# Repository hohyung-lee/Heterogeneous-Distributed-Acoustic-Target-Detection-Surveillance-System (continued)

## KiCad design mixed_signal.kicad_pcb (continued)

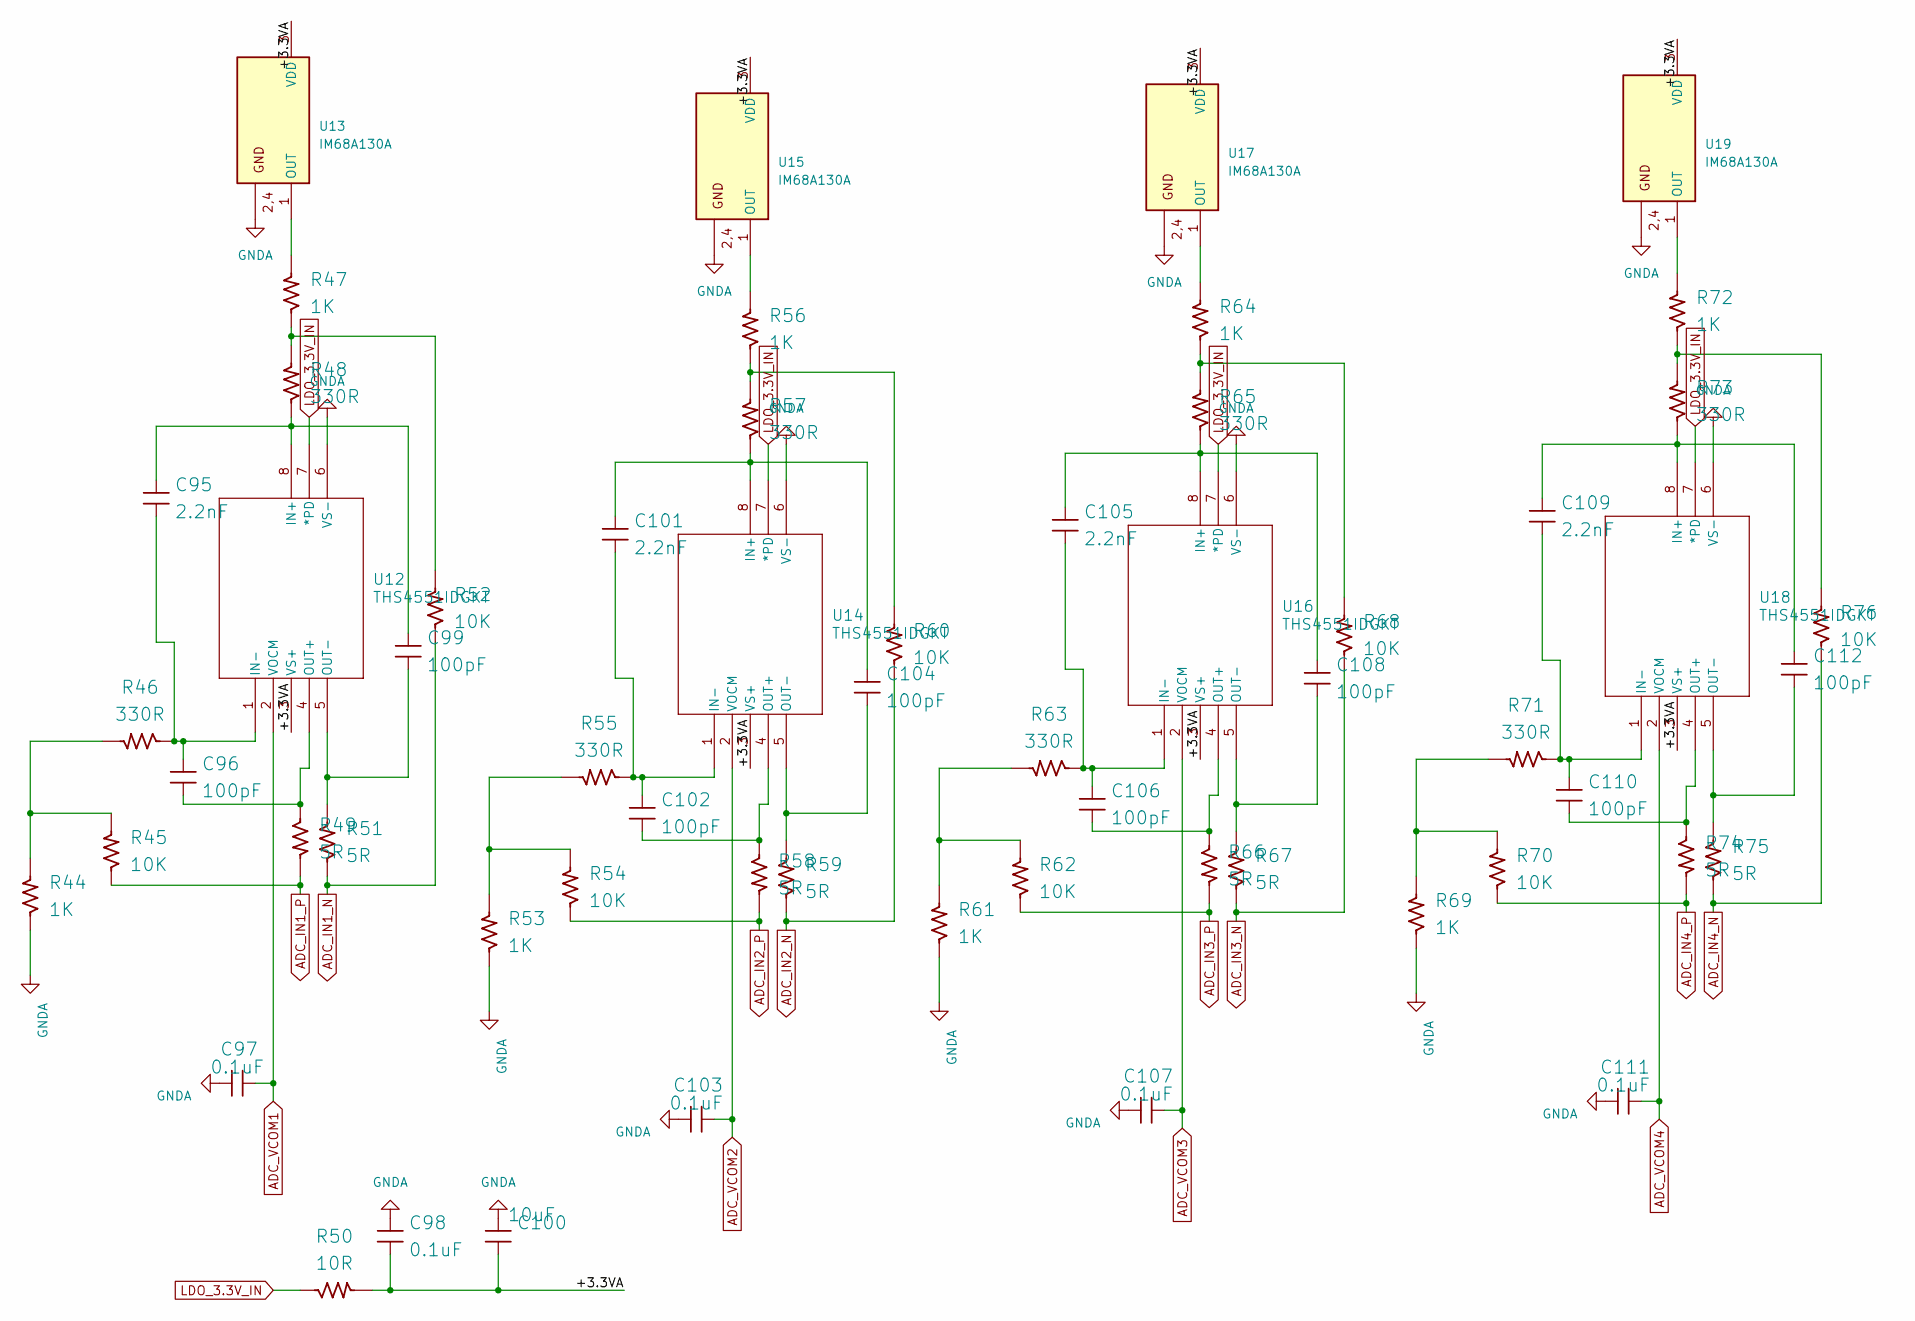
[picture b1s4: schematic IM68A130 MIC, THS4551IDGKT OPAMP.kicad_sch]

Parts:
C95, C101, C105, C109: 2.2nF; CAP_0805; Manufacturer Part Number C0805C222K5GEC7800
C96, C99, C102, C104, C106, C108, C110, C112: 100pF; CAP_0805; Manufacturer Part Number CC0805JRNPO9BN101
C97, C98, C103, C107, C111: 0.1uF; CAP_0805; Manufacturer Part Number 08055C104JAT4A
C100: 10uF; CAP_1206; Manufacturer Part Number CL31B106KBHNNNE
R44, R47, R53, R56, R61, R64, R69, R72: 1K; RES_0805; Manufacturer Part Number WR08X1001FTL
R45, R52, R54, R60, R62, R68, R70, R76: 10K; RES_0805; Manufacturer Part Number WR08X1002FTL
R46, R48, R55, R57, R63, R65, R71, R73: 330R; RES_0805; Manufacturer Part Number WR08X3300FTL
R49, R51, R58, R59, R66, R67, R74, R75: 5R; RES_0805; Manufacturer Part Number L-0805M5R00FGTS
R50: 10R; RES_0805; Manufacturer Part Number WR08X10R0FTL
U12, U14, U16, U18: THS4551IDGKT; DGK_S-PDSO-G8_TEX
U13, U15, U17, U19: IM68A130A; PAP0064G-IPC_A

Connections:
/IM68A130 MIC, THS4551IDGKT OPAMP/+3.3VA: C98.1, C100.1, R50.2, U12.3 (VS+), U13.3 (VDD), U14.3 (VS+), U15.3 (VDD), U16.3 (VS+), U17.3 (VDD), U18.3 (VS+), U19.3 (VDD)
ADC_IN1_N: R51.1, R52.1; also elsewhere on the board
ADC_IN1_P: R45.1, R49.2; also elsewhere on the board
ADC_IN2_N: R59.1, R60.1; also elsewhere on the board
ADC_IN2_P: R54.1, R58.2; also elsewhere on the board
ADC_IN3_N: R67.1, R68.1; also elsewhere on the board
ADC_IN3_P: R62.1, R66.2; also elsewhere on the board
ADC_IN4_N: R75.1, R76.1; also elsewhere on the board
ADC_IN4_P: R70.1, R74.2; also elsewhere on the board
ADC_VCOM1: C97.2, C103.2, C107.2, C111.2, U12.2 (VOCM), U14.2 (VOCM), U16.2 (VOCM), U18.2 (VOCM); also elsewhere on the board
GNDA: C97.1, C98.2, C100.2, C103.1, C107.1, C111.1, R44.1, R53.1, R61.1, R69.1, U12.6 (VS-), U13.2 (GND), U13.4 (GND), U14.6 (VS-), U15.2 (GND), U15.4 (GND), U16.6 (VS-), U17.2 (GND), U17.4 (GND), U18.6 (VS-), U19.2 (GND), U19.4 (GND); also elsewhere on the board
LDO_3.3V_IN: R50.1, U12.7 (*PD), U14.7 (*PD), U16.7 (*PD), U18.7 (*PD); also elsewhere on the board
unnamed: R44.2, R45.2, R46.2
unnamed: R47.1, R48.2, R52.2
unnamed: R53.2, R54.2, R55.2
unnamed: R56.1, R57.2, R60.2
unnamed: R61.2, R62.2, R63.2
unnamed: R64.1, R65.2, R68.2
unnamed: R69.2, R70.2, R71.2
unnamed: R72.1, R73.2, R76.2
unnamed: C95.2, C99.2, R48.1, U12.8 (IN+)
unnamed: C95.1, C96.2, R46.1, U12.1 (IN-)
unnamed: C96.1, R49.1, U12.4 (OUT+)
unnamed: C99.1, R51.2, U12.5 (OUT-)
unnamed: R47.2, U13.1 (OUT)
unnamed: C101.2, C104.2, R57.1, U14.8 (IN+)
unnamed: C101.1, C102.2, R55.1, U14.1 (IN-)
unnamed: C102.1, R58.1, U14.4 (OUT+)
unnamed: C104.1, R59.2, U14.5 (OUT-)
unnamed: R56.2, U15.1 (OUT)
unnamed: C105.2, C108.2, R65.1, U16.8 (IN+)
unnamed: C105.1, C106.2, R63.1, U16.1 (IN-)
unnamed: C106.1, R66.1, U16.4 (OUT+)
unnamed: C108.1, R67.2, U16.5 (OUT-)
unnamed: R64.2, U17.1 (OUT)
unnamed: C109.2, C112.2, R73.1, U18.8 (IN+)
unnamed: C109.1, C110.2, R71.1, U18.1 (IN-)
unnamed: C110.1, R74.1, U18.4 (OUT+)
unnamed: C112.1, R75.2, U18.5 (OUT-)
unnamed: R72.2, U19.1 (OUT)

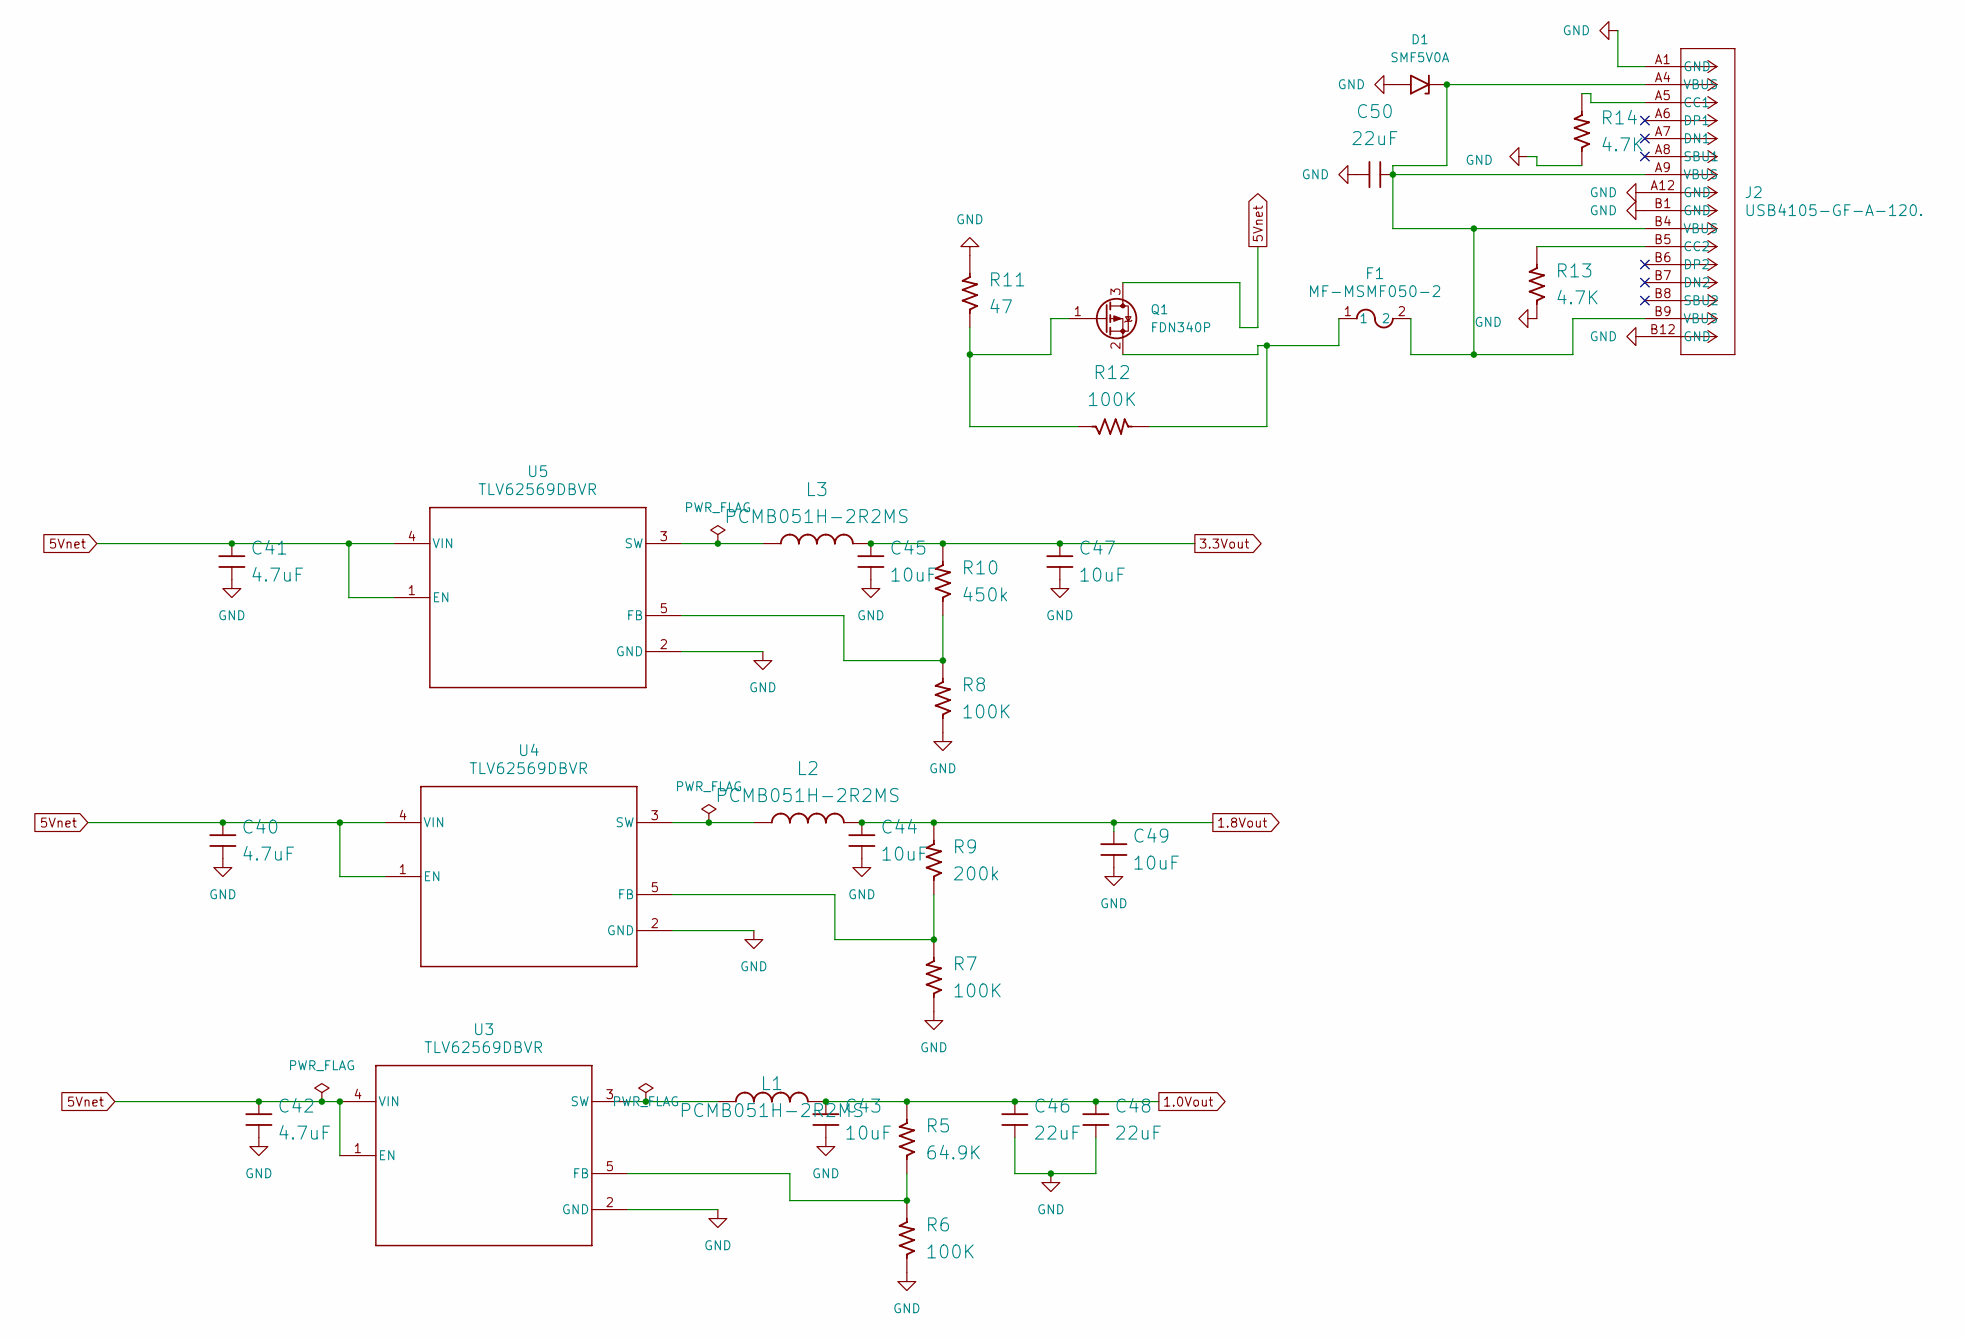
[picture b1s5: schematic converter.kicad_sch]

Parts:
C40, C41, C42: 4.7uF; CAP_0805; Manufacturer Part Number GRM21BR61H475KE51L
C43, C44, C45, C47, C49: 10uF; CAP_1206; Manufacturer Part Number CL31B106KBHNNNE
C46, C48, C50: 22uF; CAP_0805; Manufacturer Part Number GRM21BR61E226ME44L
D1: SMF5V0A; D_SMF
F1: MF-MSMF050-2; FUSE_F050-2
J2: USB4105-GF-A-120.; CONN_USB4105-xx-A-xxx_GCT
L1, L2, L3: PCMB051H-2R2MS; IND_259_338_140X70_SMD; Manufacturer Part Number PCMB051H-2R2MS
Q1: FDN340P; SOT-23
R5: 64.9K; RES_0805; Manufacturer Part Number RC0805FR-0764K9L
R6, R7, R8, R12: 100K; RES_0805; Manufacturer Part Number WR08X1003FTL
R9: 200k; RES_0805; Manufacturer Part Number RC0805FR-07523KL
R10: 450k; RES_0805; Manufacturer Part Number RC0805FR-07523KL
R11: 47; RES_0805; Manufacturer Part Number WR08X000PTL
R13, R14: 4.7K; RES_0805; Manufacturer Part Number RC0805FR-074K7L
U3, U4, U5: TLV62569DBVR; DBV0005A_N

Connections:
1.0Vout: C43.2, C46.2, C48.2, L1.2, R5.2; also elsewhere on the board
1.8Vout: C44.2, C49.2, L2.2, R9.2; also elsewhere on the board
3.3Vout: C45.2, C47.2, L3.2, R10.2; also elsewhere on the board
5Vnet: C40.2, C41.2, C42.2, Q1.3 (D), U3.1 (EN), U3.4 (VIN), U4.1 (EN), U4.4 (VIN), U5.1 (EN), U5.4 (VIN); also elsewhere on the board
+3V3: C40.1, C41.1, C42.1, C43.1, C44.1, C45.1, C46.1, C47.1, C48.1, C49.1, C50.1, D1.2 (A2), J2.A1 (GND), J2.A12 (GND), J2.B1 (GND), J2.B12 (GND), R6.1, R7.1, R8.1, R11.2, R13.1, R14.1, U3.2 (GND), U4.2 (GND), U5.2 (GND); also elsewhere on the board
unnamed: C50.2, D1.1 (A1), F1.2, J2.A4 (VBUS), J2.A9 (VBUS), J2.B4 (VBUS), J2.B9 (VBUS)
unnamed: J2.A5 (CC1), R14.2
unnamed: J2.B5 (CC2), R13.2
unnamed: Q1.1 (G), R11.1, R12.1
unnamed: F1.1, Q1.2 (S), R12.2
unnamed: R5.1, R6.2, U3.5 (FB)
unnamed: L1.1, U3.3 (SW)
unnamed: R7.2, R9.1, U4.5 (FB)
unnamed: L2.1, U4.3 (SW)
unnamed: R8.2, R10.1, U5.5 (FB)
unnamed: L3.1, U5.3 (SW)

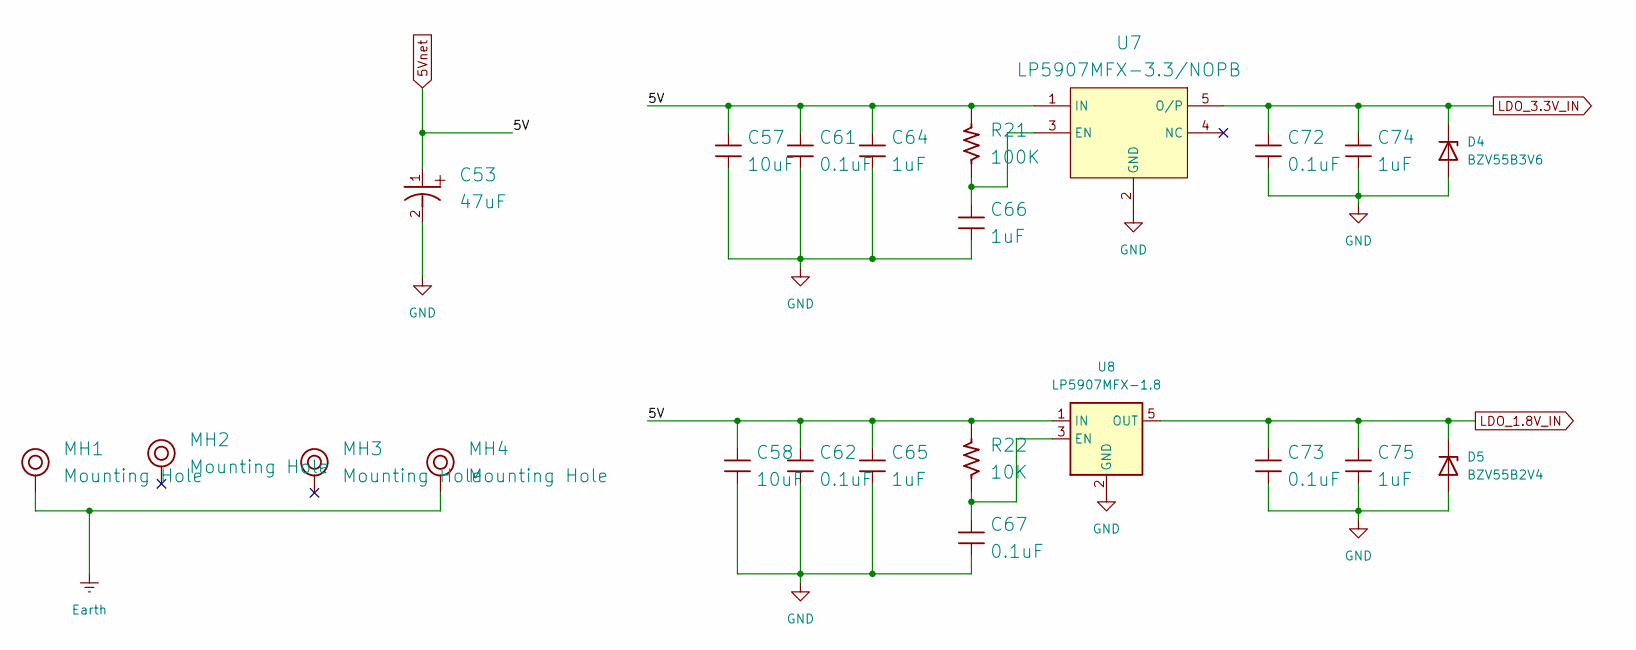
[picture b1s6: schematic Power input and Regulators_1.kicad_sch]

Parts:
C53: 47uF; C_0805_2012Metric_Pad1.18x1.45mm_HandSolder; Manufacturer Part Number EEE-1VA470WP
C57, C58: 10uF; CAP_1206; Manufacturer Part Number CL31B106KBHNNNE
C61, C62, C67, C72, C73: 0.1uF; CAP_0805; Manufacturer Part Number CL21B104KBCNNNC
C64, C65, C66, C74, C75: 1uF; CAP_0805; Manufacturer Part Number CC0805JKX7R9BB105
D4: BZV55B3V6; D_MiniMELF
D5: BZV55B2V4; D_MiniMELF
MH1, MH2, MH3, MH4: Mounting Hole; MOUNTING; Manufacturer Part Number NA
R21: 100K; RES_0603; Manufacturer Part Number RMCF0603FT100K
R22: 10K; RES_0603; Manufacturer Part Number WR06X1002FTL
U7: LP5907MFX-3.3/NOPB; SOT23-5; Manufacturer Part Number LP5907MFX-3.3/NOPB
U8: LP5907MFX-1.8; SOT-23-5

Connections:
5Vnet: C53.1, C57.2, C58.2, C61.2, C62.2, C64.2, C65.2, R21.2, R22.2, U7.1 (IN), U8.1 (IN); also elsewhere on the board
+3V3: C53.2, C57.1, C58.1, C61.1, C62.1, C64.1, C65.1, C66.1, C67.2, C72.1, C73.1, C74.1, C75.1, D4.2 (A), D5.2 (A), U7.2 (GND), U8.2 (GND); also elsewhere on the board
Earth: MH1.1, MH4.1
LDO_1.8V_IN: C73.2, C75.2, D5.1 (K), U8.5 (OUT); also elsewhere on the board
LDO_3.3V_IN: C72.2, C74.2, D4.1 (K), U7.5 (O/P); also elsewhere on the board
unnamed: C66.2, R21.1, U7.3 (EN)
unnamed: C67.1, R22.1, U8.3 (EN)

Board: 4 copper layers, 227 parts (0 on the bottom side), 133 nets, no tracks yet.

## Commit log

2026-04-02 Initial KiCad project
2026-04-02 Update gitignore for KiCad project
2026-04-02 Revise README with project details in Korean
    Updated the README to include project details in Korean, outlining the objectives, system architecture, hardware specifications, and expected impact.
